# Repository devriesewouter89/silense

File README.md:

View this project on [CADLAB.io](https://cadlab.io/project/2243). 

# silense

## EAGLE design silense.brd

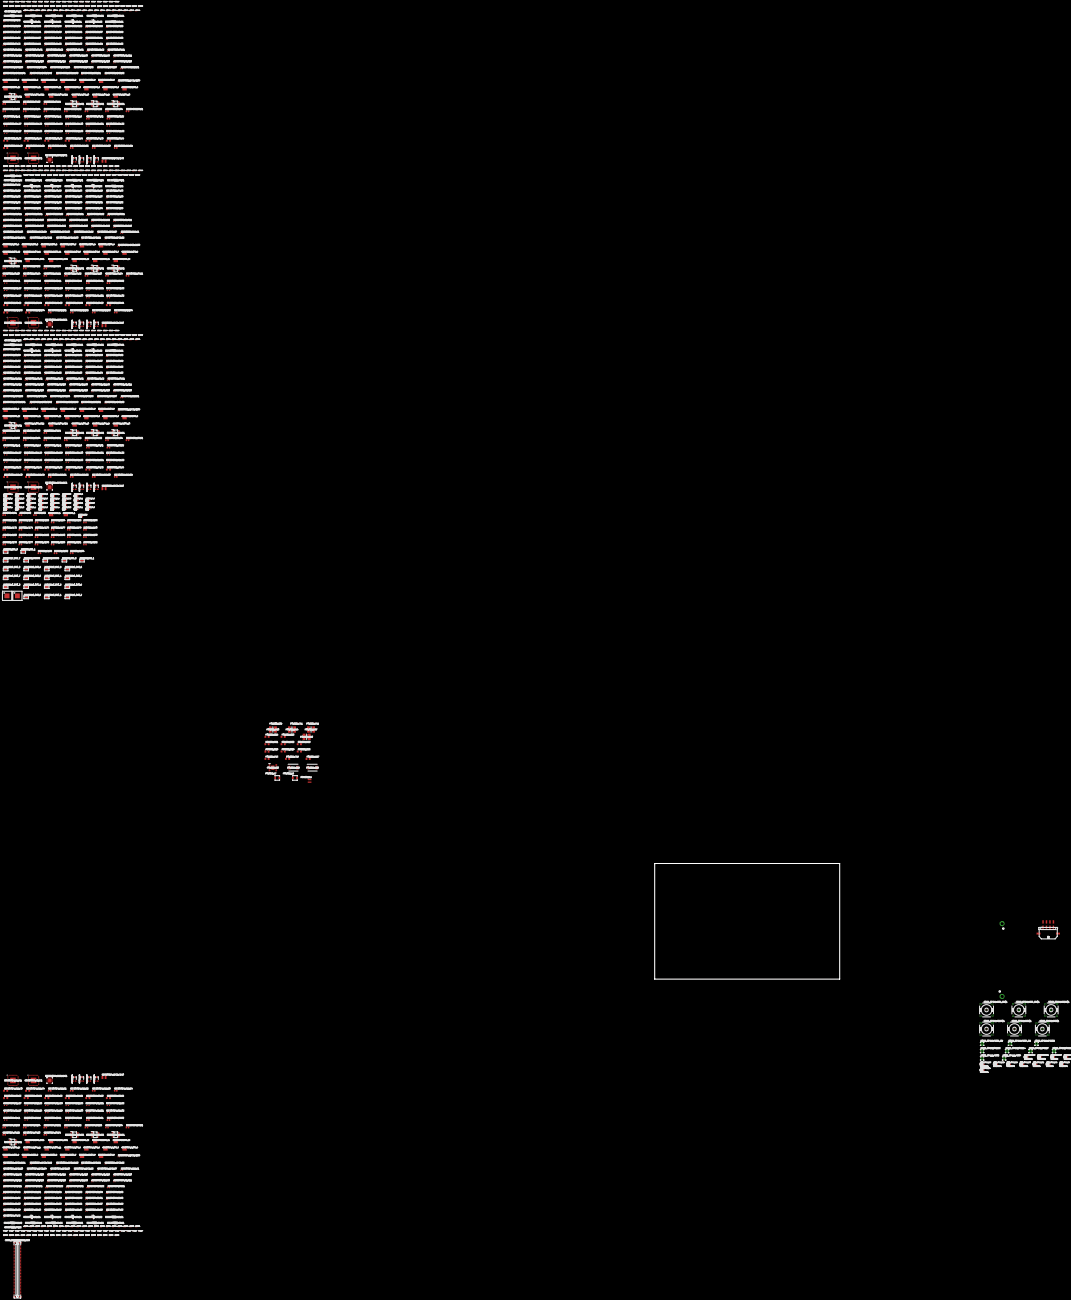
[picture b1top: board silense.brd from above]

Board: 2 copper layers, 946 parts (0 on the bottom side), 798 nets, no tracks yet.

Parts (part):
CONN_FPGA1:D3, CONN_FPGA1:D4, CONN_FPGA1:D13, CONN_FPGA1:D14, CONN_FPGA1:D17, CONN_FPGA1:D18, CONN_FPGA1:D19, CONN_FPGA1:D20: SBR1U200P1; POWERDI-123
CONN_FPGA1:D15, CONN_FPGA1:D16, CONN_FPGA1:D21, CONN_FPGA1:D22: SBR3U20SA; POWERDI-123
CONN_FPGA1:HVM$1, CONN_FPGA1:HVM_CW$1, CONN_FPGA1:HVP$1, CONN_FPGA1:HVP_CW$1, CONN_FPGA1:VDDM$1, CONN_FPGA1:VDDP$1: R141426
CONN_FPGA1:J1: FMC-LPC; FMC-LPC-MALE
CONN_FPGA1:PGND+: GND; 3,17/1,3
CONN_FPGA1:PGND-, CONN_FPGA1:PGNDD, CONN_FPGA1:PHVM, CONN_FPGA1:PHVM_CW, CONN_FPGA1:PHVP, CONN_FPGA1:PHVP_CW, CONN_FPGA1:PVDDM, CONN_FPGA1:PVDDP: 3,17/1,3
CONN_FPGA1:POWER_BOARD_CONN: 43045-0809
CONN_RESONATORS1:C30: CBEC219-3479B001C1AF; BTB_CONN_68_F
DRIVER1:C170, DRIVER1:C172, DRIVER1:C174, DRIVER1:C175, DRIVER1:C177, DRIVER1:C178, DRIVER1:C180, DRIVER1:C181, DRIVER1:C182, DRIVER1:C183, DRIVER1:C184, DRIVER1:C185, DRIVER1:C190, DRIVER1:C191, DRIVER2:C170, DRIVER2:C172, DRIVER2:C174, DRIVER2:C175, DRIVER2:C177, DRIVER2:C178, DRIVER2:C180, DRIVER2:C181, DRIVER2:C182, DRIVER2:C183, DRIVER2:C184, DRIVER2:C185, DRIVER2:C190, DRIVER2:C191: 220n 100V; C0805
DRIVER1:D0_0, DRIVER1:D0_1, DRIVER1:D1_0, DRIVER1:D1_1, DRIVER1:D2_0, DRIVER1:D2_1, DRIVER1:D3_0, DRIVER1:D3_1, DRIVER1:D4_0, DRIVER1:D4_1, DRIVER1:D5_0, DRIVER1:D5_1, DRIVER1:D6_0, DRIVER1:D6_1, DRIVER1:D7_0, DRIVER1:D7_1, DRIVER2:D0_0, DRIVER2:D0_1, DRIVER2:D1_0, DRIVER2:D1_1, DRIVER2:D2_0, DRIVER2:D2_1, DRIVER2:D3_0, DRIVER2:D3_1, DRIVER2:D4_0, DRIVER2:D4_1, DRIVER2:D5_0, DRIVER2:D5_1, DRIVER2:D6_0, DRIVER2:D6_1, DRIVER2:D7_0, DRIVER2:D7_1: POWERDI-123
DRIVER1:GND_1, DRIVER2:GND_1: 5019; TP380X203
DRIVER1:IN0_0, DRIVER1:IN0_1, DRIVER1:LVOUT0, DRIVER1:T_OUT_0, DRIVER1:T_OUT_1, DRIVER1:T_OUT_2, DRIVER1:T_OUT_3, DRIVER1:T_OUT_4, DRIVER1:T_OUT_5, DRIVER1:T_OUT_6, DRIVER1:T_OUT_7, DRIVER2:IN0_0, DRIVER2:IN0_1, DRIVER2:LVOUT0, DRIVER2:T_OUT_0, DRIVER2:T_OUT_1, DRIVER2:T_OUT_2, DRIVER2:T_OUT_3, DRIVER2:T_OUT_4, DRIVER2:T_OUT_5, DRIVER2:T_OUT_6, DRIVER2:T_OUT_7: 5015; KEYSTONE_5015
DRIVER1:R2, DRIVER2:R2: 10k; R0805
DRIVER1:STHV_0, DRIVER2:STHV_0: STHV800; TFLGA-56LD
POWER1:C39: C3216X7R1H225K160AE; CAPC3216X180N
POWER1:C40, POWER1:C43, POWER1:C44, POWER1:C47: 1206 x7r 47uF 25V; CAPC6050X550N
POWER1:C41, POWER1:C42: 0.1uF x7r 1206; CAPC3416X90N
POWER1:C45, POWER1:C46: 1206 x7r 2.2uF 25V; C1206
POWER1:D25: MBRS360T3G; DIOM7958X256N
POWER1:D26: VS-MBRS340-M3_9AT; DIOM7959X262N
POWER1:IC3: LT8471EFE#PBF; SOP65P640X120-21N
POWER1:L2: 744025150; WE-TPC_282892
POWER1:L7: 74437324068; WE-LHMI_402048
POWER1:L8: 74437324100; WE-LHMI_402048
POWER1:R17: 261k 25V; M1206
POWER1:R18: 82k 25V; M1206
POWER1:R19, POWER1:R21: 316k; R1206
POWER1:R20, POWER1:R22: 59k; R1206
POWER1:R23, POWER1:R24: 100k; R1206
POWER1:R25: 187k; R1206
RECEIVER1:ADC2:ADC1, RECEIVER2:ADC2:ADC1, RECEIVER3:ADC2:ADC1, RECEIVER4:ADC2:ADC1: LTC2344-16; QFN32
RECEIVER1:ADC2:C139, RECEIVER1:ADC2:C142, RECEIVER1:ADC2:C143, RECEIVER2:ADC2:C139, RECEIVER2:ADC2:C142, RECEIVER2:ADC2:C143, RECEIVER3:ADC2:C139, RECEIVER3:ADC2:C142, RECEIVER3:ADC2:C143, RECEIVER4:ADC2:C139, RECEIVER4:ADC2:C142, RECEIVER4:ADC2:C143: 0.1uf; C0402
RECEIVER1:ADC2:C140, RECEIVER2:ADC2:C140, RECEIVER3:ADC2:C140, RECEIVER4:ADC2:C140: 47uf 10V; C1210
RECEIVER1:ADC2:C141, RECEIVER2:ADC2:C141, RECEIVER3:ADC2:C141, RECEIVER4:ADC2:C141: 2.2uf; C0402
RECEIVER1:ADC2:R1, RECEIVER1:ADC2:R2, RECEIVER1:ADC2:R3, RECEIVER1:ADC2:R4, RECEIVER1:ADC2:R5, RECEIVER1:ADC2:R6, RECEIVER1:ADC2:R7, RECEIVER2:ADC2:R1, RECEIVER2:ADC2:R2, RECEIVER2:ADC2:R3, RECEIVER2:ADC2:R4, RECEIVER2:ADC2:R5, RECEIVER2:ADC2:R6, RECEIVER2:ADC2:R7, RECEIVER3:ADC2:R1, RECEIVER3:ADC2:R2, RECEIVER3:ADC2:R3, RECEIVER3:ADC2:R4, RECEIVER3:ADC2:R5, RECEIVER3:ADC2:R6, RECEIVER3:ADC2:R7, RECEIVER4:ADC2:R1, RECEIVER4:ADC2:R2, RECEIVER4:ADC2:R3, RECEIVER4:ADC2:R4, RECEIVER4:ADC2:R5, RECEIVER4:ADC2:R6, RECEIVER4:ADC2:R7: 33R; R0402
RECEIVER1:S1:C1, RECEIVER1:S1:C2, RECEIVER1:S1:C3, RECEIVER1:S1:C4, RECEIVER1:S1:C5, RECEIVER1:S1:C6, RECEIVER1:S1:C7, RECEIVER1:S1:C8, RECEIVER1:S1:C9, RECEIVER1:S1:C10, RECEIVER1:S1:C13, RECEIVER1:S1:C14, RECEIVER1:S1:C15, RECEIVER1:S1:C16, RECEIVER1:S1:C17, RECEIVER1:S1:C18, RECEIVER1:S1:C21, RECEIVER1:S1:C22, RECEIVER1:S1:C23, RECEIVER1:S1:C26, RECEIVER1:S1:C51, RECEIVER1:S1:C52, RECEIVER1:S1:C53, RECEIVER1:S1:C54, RECEIVER1:S1:C55, RECEIVER1:S1:C56, RECEIVER1:S2:C1, RECEIVER1:S2:C2, RECEIVER1:S2:C3, RECEIVER1:S2:C4, RECEIVER1:S2:C5, RECEIVER1:S2:C6, RECEIVER1:S2:C7, RECEIVER1:S2:C8, RECEIVER1:S2:C9, RECEIVER1:S2:C10, RECEIVER1:S2:C13, RECEIVER1:S2:C14, RECEIVER1:S2:C15, RECEIVER1:S2:C16, RECEIVER1:S2:C17, RECEIVER1:S2:C18, RECEIVER1:S2:C21, RECEIVER1:S2:C22, RECEIVER1:S2:C23, RECEIVER1:S2:C26, RECEIVER1:S2:C51, RECEIVER1:S2:C52, RECEIVER1:S2:C53, RECEIVER1:S2:C54, RECEIVER1:S2:C55, RECEIVER1:S2:C56, RECEIVER2:S1:C1, RECEIVER2:S1:C2, RECEIVER2:S1:C3, RECEIVER2:S1:C4, RECEIVER2:S1:C5, RECEIVER2:S1:C6, RECEIVER2:S1:C7, RECEIVER2:S1:C8, RECEIVER2:S1:C9, RECEIVER2:S1:C10, RECEIVER2:S1:C13, RECEIVER2:S1:C14, RECEIVER2:S1:C15, RECEIVER2:S1:C16, RECEIVER2:S1:C17, RECEIVER2:S1:C18, RECEIVER2:S1:C21, RECEIVER2:S1:C22, RECEIVER2:S1:C23, RECEIVER2:S1:C26, RECEIVER2:S1:C51, RECEIVER2:S1:C52, RECEIVER2:S1:C53, RECEIVER2:S1:C54, RECEIVER2:S1:C55, RECEIVER2:S1:C56, RECEIVER2:S2:C1, RECEIVER2:S2:C2, RECEIVER2:S2:C3, RECEIVER2:S2:C4, RECEIVER2:S2:C5, RECEIVER2:S2:C6, RECEIVER2:S2:C7, RECEIVER2:S2:C8, RECEIVER2:S2:C9, RECEIVER2:S2:C10, RECEIVER2:S2:C13, RECEIVER2:S2:C14, RECEIVER2:S2:C15, RECEIVER2:S2:C16, RECEIVER2:S2:C17, RECEIVER2:S2:C18, RECEIVER2:S2:C21, RECEIVER2:S2:C22, RECEIVER2:S2:C23, RECEIVER2:S2:C26, RECEIVER2:S2:C51, RECEIVER2:S2:C52, RECEIVER2:S2:C53, RECEIVER2:S2:C54, RECEIVER2:S2:C55, RECEIVER2:S2:C56, RECEIVER3:S1:C1, RECEIVER3:S1:C2, RECEIVER3:S1:C3, RECEIVER3:S1:C4, RECEIVER3:S1:C5, RECEIVER3:S1:C6, RECEIVER3:S1:C7, RECEIVER3:S1:C8, RECEIVER3:S1:C9, RECEIVER3:S1:C10, RECEIVER3:S1:C13, RECEIVER3:S1:C14, RECEIVER3:S1:C15, RECEIVER3:S1:C16, RECEIVER3:S1:C17, RECEIVER3:S1:C18, RECEIVER3:S1:C21, RECEIVER3:S1:C22, RECEIVER3:S1:C23, RECEIVER3:S1:C26, RECEIVER3:S1:C51, RECEIVER3:S1:C52, RECEIVER3:S1:C53, RECEIVER3:S1:C54, RECEIVER3:S1:C55, RECEIVER3:S1:C56, RECEIVER3:S2:C1, RECEIVER3:S2:C2, RECEIVER3:S2:C3, RECEIVER3:S2:C4, RECEIVER3:S2:C5, RECEIVER3:S2:C6, RECEIVER3:S2:C7, RECEIVER3:S2:C8, RECEIVER3:S2:C9, RECEIVER3:S2:C10, RECEIVER3:S2:C13, RECEIVER3:S2:C14, RECEIVER3:S2:C15, RECEIVER3:S2:C16, RECEIVER3:S2:C17, RECEIVER3:S2:C18, RECEIVER3:S2:C21, RECEIVER3:S2:C22, RECEIVER3:S2:C23, RECEIVER3:S2:C26, RECEIVER3:S2:C51, RECEIVER3:S2:C52, RECEIVER3:S2:C53, RECEIVER3:S2:C54, RECEIVER3:S2:C55, RECEIVER3:S2:C56, RECEIVER4:S1:C1, RECEIVER4:S1:C2, RECEIVER4:S1:C3, RECEIVER4:S1:C4, RECEIVER4:S1:C5, RECEIVER4:S1:C6, RECEIVER4:S1:C7, RECEIVER4:S1:C8, RECEIVER4:S1:C9, RECEIVER4:S1:C10, RECEIVER4:S1:C13, RECEIVER4:S1:C14, RECEIVER4:S1:C15, RECEIVER4:S1:C16, RECEIVER4:S1:C17, RECEIVER4:S1:C18, RECEIVER4:S1:C21, RECEIVER4:S1:C22, RECEIVER4:S1:C23, RECEIVER4:S1:C26, RECEIVER4:S1:C51, RECEIVER4:S1:C52, RECEIVER4:S1:C53, RECEIVER4:S1:C54, RECEIVER4:S1:C55, RECEIVER4:S1:C56, RECEIVER4:S2:C1, RECEIVER4:S2:C2, RECEIVER4:S2:C3, RECEIVER4:S2:C4, RECEIVER4:S2:C5, RECEIVER4:S2:C6, RECEIVER4:S2:C7, RECEIVER4:S2:C8, RECEIVER4:S2:C9, RECEIVER4:S2:C10, RECEIVER4:S2:C13, RECEIVER4:S2:C14, RECEIVER4:S2:C15, RECEIVER4:S2:C16, RECEIVER4:S2:C17, RECEIVER4:S2:C18, RECEIVER4:S2:C21, RECEIVER4:S2:C22, RECEIVER4:S2:C23, RECEIVER4:S2:C26, RECEIVER4:S2:C51, RECEIVER4:S2:C52, RECEIVER4:S2:C53, RECEIVER4:S2:C54, RECEIVER4:S2:C55, RECEIVER4:S2:C56: 0.1uF; WCAP-CSGP_0402
RECEIVER1:S1:C11, RECEIVER1:S1:C12, RECEIVER1:S2:C11, RECEIVER1:S2:C12, RECEIVER2:S1:C11, RECEIVER2:S1:C12, RECEIVER2:S2:C11, RECEIVER2:S2:C12, RECEIVER3:S1:C11, RECEIVER3:S1:C12, RECEIVER3:S2:C11, RECEIVER3:S2:C12, RECEIVER4:S1:C11, RECEIVER4:S1:C12, RECEIVER4:S2:C11, RECEIVER4:S2:C12: 18nF; WCAP-CSGP_0402
RECEIVER1:S1:C19, RECEIVER1:S1:C20, RECEIVER1:S2:C19, RECEIVER1:S2:C20, RECEIVER2:S1:C19, RECEIVER2:S1:C20, RECEIVER2:S2:C19, RECEIVER2:S2:C20, RECEIVER3:S1:C19, RECEIVER3:S1:C20, RECEIVER3:S2:C19, RECEIVER3:S2:C20, RECEIVER4:S1:C19, RECEIVER4:S1:C20, RECEIVER4:S2:C19, RECEIVER4:S2:C20: 10nF; WCAP-CSGP_0402
RECEIVER1:S1:C24, RECEIVER1:S1:C27, RECEIVER1:S2:C24, RECEIVER1:S2:C27, RECEIVER2:S1:C24, RECEIVER2:S1:C27, RECEIVER2:S2:C24, RECEIVER2:S2:C27, RECEIVER3:S1:C24, RECEIVER3:S1:C27, RECEIVER3:S2:C24, RECEIVER3:S2:C27, RECEIVER4:S1:C24, RECEIVER4:S1:C27, RECEIVER4:S2:C24, RECEIVER4:S2:C27: 22pF; WCAP-CSGP_0402
RECEIVER1:S1:D1, RECEIVER1:S1:D2, RECEIVER1:S2:D1, RECEIVER1:S2:D2, RECEIVER2:S1:D1, RECEIVER2:S1:D2, RECEIVER2:S2:D1, RECEIVER2:S2:D2, RECEIVER3:S1:D1, RECEIVER3:S1:D2, RECEIVER3:S2:D1, RECEIVER3:S2:D2, RECEIVER4:S1:D1, RECEIVER4:S1:D2, RECEIVER4:S2:D1, RECEIVER4:S2:D2: BAT64-04E6433; SOT95P260X110-3N
RECEIVER1:S1:IC1, RECEIVER1:S2:IC1, RECEIVER2:S1:IC1, RECEIVER2:S2:IC1, RECEIVER3:S1:IC1, RECEIVER3:S2:IC1, RECEIVER4:S1:IC1, RECEIVER4:S2:IC1: AD8334ACPZ; QFN50P900X900X100-65N
RECEIVER1:S1:L1, RECEIVER1:S1:L6, RECEIVER1:S1:L27, RECEIVER1:S1:L28, RECEIVER1:S1:L29, RECEIVER1:S1:L30, RECEIVER1:S1:L31, RECEIVER1:S1:L32, RECEIVER1:S2:L1, RECEIVER1:S2:L6, RECEIVER1:S2:L27, RECEIVER1:S2:L28, RECEIVER1:S2:L29, RECEIVER1:S2:L30, RECEIVER1:S2:L31, RECEIVER1:S2:L32, RECEIVER2:S1:L1, RECEIVER2:S1:L6, RECEIVER2:S1:L27, RECEIVER2:S1:L28, RECEIVER2:S1:L29, RECEIVER2:S1:L30, RECEIVER2:S1:L31, RECEIVER2:S1:L32, RECEIVER2:S2:L1, RECEIVER2:S2:L6, RECEIVER2:S2:L27, RECEIVER2:S2:L28, RECEIVER2:S2:L29, RECEIVER2:S2:L30, RECEIVER2:S2:L31, RECEIVER2:S2:L32, RECEIVER3:S1:L1, RECEIVER3:S1:L6, RECEIVER3:S1:L27, RECEIVER3:S1:L28, RECEIVER3:S1:L29, RECEIVER3:S1:L30, RECEIVER3:S1:L31, RECEIVER3:S1:L32, RECEIVER3:S2:L1, RECEIVER3:S2:L6, RECEIVER3:S2:L27, RECEIVER3:S2:L28, RECEIVER3:S2:L29, RECEIVER3:S2:L30, RECEIVER3:S2:L31, RECEIVER3:S2:L32, RECEIVER4:S1:L1, RECEIVER4:S1:L6, RECEIVER4:S1:L27, RECEIVER4:S1:L28, RECEIVER4:S1:L29, RECEIVER4:S1:L30, RECEIVER4:S1:L31, RECEIVER4:S1:L32, RECEIVER4:S2:L1, RECEIVER4:S2:L6, RECEIVER4:S2:L27, RECEIVER4:S2:L28, RECEIVER4:S2:L29, RECEIVER4:S2:L30, RECEIVER4:S2:L31, RECEIVER4:S2:L32: BLM21AG121SN1D; L2012C
RECEIVER1:S1:R1, RECEIVER1:S1:R3, RECEIVER1:S2:R1, RECEIVER1:S2:R3, RECEIVER2:S1:R1, RECEIVER2:S1:R3, RECEIVER2:S2:R1, RECEIVER2:S2:R3, RECEIVER3:S1:R1, RECEIVER3:S1:R3, RECEIVER3:S2:R1, RECEIVER3:S2:R3, RECEIVER4:S1:R1, RECEIVER4:S1:R3, RECEIVER4:S2:R1, RECEIVER4:S2:R3: 39K; R0402
RECEIVER1:S1:R2, RECEIVER1:S1:R7, RECEIVER1:S1:R8, RECEIVER1:S1:R11, RECEIVER1:S2:R2, RECEIVER1:S2:R7, RECEIVER1:S2:R8, RECEIVER1:S2:R11, RECEIVER2:S1:R2, RECEIVER2:S1:R7, RECEIVER2:S1:R8, RECEIVER2:S1:R11, RECEIVER2:S2:R2, RECEIVER2:S2:R7, RECEIVER2:S2:R8, RECEIVER2:S2:R11, RECEIVER3:S1:R2, RECEIVER3:S1:R7, RECEIVER3:S1:R8, RECEIVER3:S1:R11, RECEIVER3:S2:R2, RECEIVER3:S2:R7, RECEIVER3:S2:R8, RECEIVER3:S2:R11, RECEIVER4:S1:R2, RECEIVER4:S1:R7, RECEIVER4:S1:R8, RECEIVER4:S1:R11, RECEIVER4:S2:R2, RECEIVER4:S2:R7, RECEIVER4:S2:R8, RECEIVER4:S2:R11: 0R; R0402
RECEIVER1:S1:R4, RECEIVER1:S1:R5, RECEIVER1:S2:R4, RECEIVER1:S2:R5, RECEIVER2:S1:R4, RECEIVER2:S1:R5, RECEIVER2:S2:R4, RECEIVER2:S2:R5, RECEIVER3:S1:R4, RECEIVER3:S1:R5, RECEIVER3:S2:R4, RECEIVER3:S2:R5, RECEIVER4:S1:R4, RECEIVER4:S1:R5, RECEIVER4:S2:R4, RECEIVER4:S2:R5: 4K02; R0402
RECEIVER1:S1:R6, RECEIVER1:S1:R10, RECEIVER1:S2:R6, RECEIVER1:S2:R10, RECEIVER2:S1:R6, RECEIVER2:S1:R10, RECEIVER2:S2:R6, RECEIVER2:S2:R10, RECEIVER3:S1:R6, RECEIVER3:S1:R10, RECEIVER3:S2:R6, RECEIVER3:S2:R10, RECEIVER4:S1:R6, RECEIVER4:S1:R10, RECEIVER4:S2:R6, RECEIVER4:S2:R10: DNP; R0402
RECEIVER1:S1:R9, RECEIVER1:S1:R13, RECEIVER1:S2:R9, RECEIVER1:S2:R13, RECEIVER2:S1:R9, RECEIVER2:S1:R13, RECEIVER2:S2:R9, RECEIVER2:S2:R13, RECEIVER3:S1:R9, RECEIVER3:S1:R13, RECEIVER3:S2:R9, RECEIVER3:S2:R13, RECEIVER4:S1:R9, RECEIVER4:S1:R13, RECEIVER4:S2:R9, RECEIVER4:S2:R13: 1K; R0402
RECEIVER1:S1:R12, RECEIVER1:S1:R15, RECEIVER1:S2:R12, RECEIVER1:S2:R15, RECEIVER2:S1:R12, RECEIVER2:S1:R15, RECEIVER2:S2:R12, RECEIVER2:S2:R15, RECEIVER3:S1:R12, RECEIVER3:S1:R15, RECEIVER3:S2:R12, RECEIVER3:S2:R15, RECEIVER4:S1:R12, RECEIVER4:S1:R15, RECEIVER4:S2:R12, RECEIVER4:S2:R15: 274R; R0402
RECEIVER1:S1:TP2_5, RECEIVER1:S1:TP2_6, RECEIVER1:S1:TP2_7, RECEIVER1:S1:TP2_8, RECEIVER1:S1:TP2_9, RECEIVER1:S1:TP2_10, RECEIVER1:S1:TP2_11, RECEIVER1:S1:TP2_12, RECEIVER1:S1:TP2_GND1, RECEIVER1:S2:TP2_5, RECEIVER1:S2:TP2_6, RECEIVER1:S2:TP2_7, RECEIVER1:S2:TP2_8, RECEIVER1:S2:TP2_9, RECEIVER1:S2:TP2_10, RECEIVER1:S2:TP2_11, RECEIVER1:S2:TP2_12, RECEIVER1:S2:TP2_GND1, RECEIVER2:S1:TP2_5, RECEIVER2:S1:TP2_6, RECEIVER2:S1:TP2_7, RECEIVER2:S1:TP2_8, RECEIVER2:S1:TP2_9, RECEIVER2:S1:TP2_10, RECEIVER2:S1:TP2_11, RECEIVER2:S1:TP2_12, RECEIVER2:S1:TP2_GND1, RECEIVER2:S2:TP2_5, RECEIVER2:S2:TP2_6, RECEIVER2:S2:TP2_7, RECEIVER2:S2:TP2_8, RECEIVER2:S2:TP2_9, RECEIVER2:S2:TP2_10, RECEIVER2:S2:TP2_11, RECEIVER2:S2:TP2_12, RECEIVER2:S2:TP2_GND1, RECEIVER3:S1:TP2_5, RECEIVER3:S1:TP2_6, RECEIVER3:S1:TP2_7, RECEIVER3:S1:TP2_8, RECEIVER3:S1:TP2_9, RECEIVER3:S1:TP2_10, RECEIVER3:S1:TP2_11, RECEIVER3:S1:TP2_12, RECEIVER3:S1:TP2_GND1, RECEIVER3:S2:TP2_5, RECEIVER3:S2:TP2_6, RECEIVER3:S2:TP2_7, RECEIVER3:S2:TP2_8, RECEIVER3:S2:TP2_9, RECEIVER3:S2:TP2_10, RECEIVER3:S2:TP2_11, RECEIVER3:S2:TP2_12, RECEIVER3:S2:TP2_GND1, RECEIVER4:S1:TP2_5, RECEIVER4:S1:TP2_6, RECEIVER4:S1:TP2_7, RECEIVER4:S1:TP2_8, RECEIVER4:S1:TP2_9, RECEIVER4:S1:TP2_10, RECEIVER4:S1:TP2_11, RECEIVER4:S1:TP2_12, RECEIVER4:S1:TP2_GND1, RECEIVER4:S2:TP2_5, RECEIVER4:S2:TP2_6, RECEIVER4:S2:TP2_7, RECEIVER4:S2:TP2_8, RECEIVER4:S2:TP2_9, RECEIVER4:S2:TP2_10, RECEIVER4:S2:TP2_11, RECEIVER4:S2:TP2_12, RECEIVER4:S2:TP2_GND1: 5019; TP380X203
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
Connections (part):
BUSY: CONN_FPGA1:J1.C26, CONN_FPGA1:J1.C27, CONN_FPGA1:J1.D26, CONN_FPGA1:J1.D27, RECEIVER1:ADC2:R2.2, RECEIVER2:ADC2:R2.2, RECEIVER3:ADC2:R2.2, RECEIVER4:ADC2:R2.2
CNV: CONN_FPGA1:J1.G36, CONN_FPGA1:J1.G37, CONN_FPGA1:J1.H37, CONN_FPGA1:J1.H38, RECEIVER1:ADC2:ADC1.15, RECEIVER2:ADC2:ADC1.15, RECEIVER3:ADC2:ADC1.15, RECEIVER4:ADC2:ADC1.15
CONN_FPGA1:3P3V: CONN_FPGA1:J1.C39, CONN_FPGA1:J1.D40
CONN_FPGA1:GND: CONN_FPGA1:HVM$1.2, CONN_FPGA1:HVM$1.3, CONN_FPGA1:HVM$1.4, CONN_FPGA1:HVM$1.5, CONN_FPGA1:HVM_CW$1.2, CONN_FPGA1:HVM_CW$1.3, CONN_FPGA1:HVM_CW$1.4, CONN_FPGA1:HVM_CW$1.5, CONN_FPGA1:HVP$1.2, CONN_FPGA1:HVP$1.3, CONN_FPGA1:HVP$1.4, CONN_FPGA1:HVP$1.5, CONN_FPGA1:HVP_CW$1.2, CONN_FPGA1:HVP_CW$1.3, CONN_FPGA1:HVP_CW$1.4, CONN_FPGA1:HVP_CW$1.5, CONN_FPGA1:J1.C1, CONN_FPGA1:J1.C4, CONN_FPGA1:J1.C5, CONN_FPGA1:J1.C8, CONN_FPGA1:J1.C9, CONN_FPGA1:J1.C12, CONN_FPGA1:J1.C13, CONN_FPGA1:J1.C16, CONN_FPGA1:J1.C17, CONN_FPGA1:J1.C20, CONN_FPGA1:J1.C21, CONN_FPGA1:J1.C24, CONN_FPGA1:J1.C25, CONN_FPGA1:J1.C28, CONN_FPGA1:J1.C29, CONN_FPGA1:J1.C32, CONN_FPGA1:J1.C33, CONN_FPGA1:J1.C36, CONN_FPGA1:J1.C38, CONN_FPGA1:J1.C40, CONN_FPGA1:J1.D2, CONN_FPGA1:J1.D3, CONN_FPGA1:J1.D6, CONN_FPGA1:J1.D7, CONN_FPGA1:J1.D10, CONN_FPGA1:J1.D13, CONN_FPGA1:J1.D16, CONN_FPGA1:J1.D19, CONN_FPGA1:J1.D22, CONN_FPGA1:J1.D25, CONN_FPGA1:J1.D28, CONN_FPGA1:J1.D37, CONN_FPGA1:J1.D39, CONN_FPGA1:J1.G1, CONN_FPGA1:J1.H3, CONN_FPGA1:J1.H6, CONN_FPGA1:J1.H9, CONN_FPGA1:J1.H12, CONN_FPGA1:J1.H15, CONN_FPGA1:J1.H18, CONN_FPGA1:J1.H21, CONN_FPGA1:J1.H24, CONN_FPGA1:J1.H27, CONN_FPGA1:J1.H30, CONN_FPGA1:J1.H33, CONN_FPGA1:J1.H36, CONN_FPGA1:J1.H39, CONN_FPGA1:PGND+.1, CONN_FPGA1:PGND-.1, CONN_FPGA1:PGNDD.1, CONN_FPGA1:POWER_BOARD_CONN.P$4, CONN_FPGA1:POWER_BOARD_CONN.P$8, CONN_FPGA1:VDDM$1.2, CONN_FPGA1:VDDM$1.3, CONN_FPGA1:VDDM$1.4, CONN_FPGA1:VDDM$1.5, CONN_FPGA1:VDDP$1.2, CONN_FPGA1:VDDP$1.3, CONN_FPGA1:VDDP$1.4, CONN_FPGA1:VDDP$1.5
CONN_FPGA1:HVM: CONN_FPGA1:D4.A, CONN_FPGA1:D18.A, CONN_FPGA1:POWER_BOARD_CONN.P$5
CONN_FPGA1:HVM_CW: CONN_FPGA1:D3.A, CONN_FPGA1:D17.A, CONN_FPGA1:POWER_BOARD_CONN.P$6
CONN_FPGA1:HVP: CONN_FPGA1:D13.C, CONN_FPGA1:D19.C, CONN_FPGA1:POWER_BOARD_CONN.P$1
CONN_FPGA1:HVP_CW: CONN_FPGA1:D14.C, CONN_FPGA1:D20.C, CONN_FPGA1:POWER_BOARD_CONN.P$2
CONN_FPGA1:N$1: CONN_FPGA1:J1.G4, CONN_FPGA1:J1.G5, CONN_FPGA1:J1.G8, CONN_FPGA1:J1.G11, CONN_FPGA1:J1.G14, CONN_FPGA1:J1.G17, CONN_FPGA1:J1.G20, CONN_FPGA1:J1.G23, CONN_FPGA1:J1.G26, CONN_FPGA1:J1.G29, CONN_FPGA1:J1.G32, CONN_FPGA1:J1.G35, CONN_FPGA1:J1.G38, CONN_FPGA1:J1.G40
CONN_FPGA1:N$3: CONN_FPGA1:D17.C, CONN_FPGA1:PHVM_CW.1
CONN_FPGA1:N$4: CONN_FPGA1:D18.C, CONN_FPGA1:PHVM.1
CONN_FPGA1:N$17: CONN_FPGA1:D3.C, CONN_FPGA1:HVM_CW$1.1
CONN_FPGA1:N$18: CONN_FPGA1:D4.C, CONN_FPGA1:HVM$1.1
CONN_FPGA1:N$19: CONN_FPGA1:D13.A, CONN_FPGA1:HVP$1.1
CONN_FPGA1:N$20: CONN_FPGA1:D14.A, CONN_FPGA1:HVP_CW$1.1
CONN_FPGA1:N$21: CONN_FPGA1:D15.A, CONN_FPGA1:VDDP$1.1
CONN_FPGA1:N$22: CONN_FPGA1:D16.C, CONN_FPGA1:VDDM$1.1
CONN_FPGA1:N$25: CONN_FPGA1:D19.A, CONN_FPGA1:PHVP.1
CONN_FPGA1:N$26: CONN_FPGA1:D20.A, CONN_FPGA1:PHVP_CW.1
CONN_FPGA1:N$27: CONN_FPGA1:D21.A, CONN_FPGA1:PVDDP.1
CONN_FPGA1:N$28: CONN_FPGA1:D22.C, CONN_FPGA1:PVDDM.1
CONN_FPGA1:VDDM: CONN_FPGA1:D16.A, CONN_FPGA1:D22.A, CONN_FPGA1:POWER_BOARD_CONN.P$7
CONN_FPGA1:VDDP: CONN_FPGA1:D15.C, CONN_FPGA1:D21.C, CONN_FPGA1:POWER_BOARD_CONN.P$3
CONN_RESONATORS1:GND: CONN_RESONATORS1:C30.1, CONN_RESONATORS1:C30.34, CONN_RESONATORS1:C30.35, CONN_RESONATORS1:C30.68
CW: CONN_FPGA1:J1.H31, DRIVER1:STHV_0.CW, DRIVER2:STHV_0.CW
DRIVER1:GND: DRIVER1:C170.2, DRIVER1:C172.1, DRIVER1:C174.1, DRIVER1:C175.1, DRIVER1:C177.1, DRIVER1:C178.1, DRIVER1:C180.2, DRIVER1:C181.2, DRIVER1:C182.2, DRIVER1:C183.2, DRIVER1:C184.2, DRIVER1:C185.2, DRIVER1:C190.1, DRIVER1:C191.1, DRIVER1:GND_1.1, DRIVER1:STHV_0.AGND, DRIVER1:STHV_0.DGND, DRIVER1:STHV_0.GND_PWR@1, DRIVER1:STHV_0.GND_PWR@2, DRIVER1:STHV_0.GND_PWR@3, DRIVER1:STHV_0.GND_PWR@4
DRIVER1:HVM: DRIVER1:C183.1, DRIVER1:C184.1, DRIVER1:C185.1, DRIVER1:D0_1.A, DRIVER1:D1_1.A, DRIVER1:D2_1.A, DRIVER1:D3_1.A, DRIVER1:D4_1.A, DRIVER1:D5_1.A, DRIVER1:D6_1.A, DRIVER1:D7_1.A, DRIVER1:STHV_0.HVM@1, DRIVER1:STHV_0.HVM@2, DRIVER1:STHV_0.HVM@3, DRIVER1:STHV_0.HVM@4, DRIVER1:STHV_0.HVM@5
DRIVER1:HVM_CW: DRIVER1:C190.2, DRIVER1:C191.2, DRIVER1:STHV_0.HVM_CW
DRIVER1:HVP: DRIVER1:C172.2, DRIVER1:C174.2, DRIVER1:C175.2, DRIVER1:D0_0.C, DRIVER1:D1_0.C, DRIVER1:D2_0.C, DRIVER1:D3_0.C, DRIVER1:D4_0.C, DRIVER1:D5_0.C, DRIVER1:D6_0.C, DRIVER1:D7_0.C, DRIVER1:STHV_0.HVP@1, DRIVER1:STHV_0.HVP@2, DRIVER1:STHV_0.HVP@3, DRIVER1:STHV_0.HVP@4, DRIVER1:STHV_0.HVP@5
DRIVER1:HVP_CW: DRIVER1:C177.2, DRIVER1:C178.2, DRIVER1:STHV_0.HVP_CW
DRIVER1:N$23: DRIVER1:R2.1, DRIVER1:STHV_0.THSD
DRIVER1:N$24: DRIVER1:C170.1, DRIVER1:STHV_0.SUB
DRIVER1:VDDM: DRIVER1:C181.1, DRIVER1:STHV_0.VDDM
DRIVER1:VDDP: DRIVER1:C180.1, DRIVER1:C182.1, DRIVER1:R2.2, DRIVER1:STHV_0.DVDD, DRIVER1:STHV_0.VDDP
DRIVER2:GND: DRIVER2:C170.2, DRIVER2:C172.1, DRIVER2:C174.1, DRIVER2:C175.1, DRIVER2:C177.1, DRIVER2:C178.1, DRIVER2:C180.2, DRIVER2:C181.2, DRIVER2:C182.2, DRIVER2:C183.2, DRIVER2:C184.2, DRIVER2:C185.2, DRIVER2:C190.1, DRIVER2:C191.1, DRIVER2:GND_1.1, DRIVER2:STHV_0.AGND, DRIVER2:STHV_0.DGND, DRIVER2:STHV_0.GND_PWR@1, DRIVER2:STHV_0.GND_PWR@2, DRIVER2:STHV_0.GND_PWR@3, DRIVER2:STHV_0.GND_PWR@4
DRIVER2:HVM: DRIVER2:C183.1, DRIVER2:C184.1, DRIVER2:C185.1, DRIVER2:D0_1.A, DRIVER2:D1_1.A, DRIVER2:D2_1.A, DRIVER2:D3_1.A, DRIVER2:D4_1.A, DRIVER2:D5_1.A, DRIVER2:D6_1.A, DRIVER2:D7_1.A, DRIVER2:STHV_0.HVM@1, DRIVER2:STHV_0.HVM@2, DRIVER2:STHV_0.HVM@3, DRIVER2:STHV_0.HVM@4, DRIVER2:STHV_0.HVM@5
DRIVER2:HVM_CW: DRIVER2:C190.2, DRIVER2:C191.2, DRIVER2:STHV_0.HVM_CW
DRIVER2:HVP: DRIVER2:C172.2, DRIVER2:C174.2, DRIVER2:C175.2, DRIVER2:D0_0.C, DRIVER2:D1_0.C, DRIVER2:D2_0.C, DRIVER2:D3_0.C, DRIVER2:D4_0.C, DRIVER2:D5_0.C, DRIVER2:D6_0.C, DRIVER2:D7_0.C, DRIVER2:STHV_0.HVP@1, DRIVER2:STHV_0.HVP@2, DRIVER2:STHV_0.HVP@3, DRIVER2:STHV_0.HVP@4, DRIVER2:STHV_0.HVP@5
DRIVER2:HVP_CW: DRIVER2:C177.2, DRIVER2:C178.2, DRIVER2:STHV_0.HVP_CW
DRIVER2:N$23: DRIVER2:R2.1, DRIVER2:STHV_0.THSD
DRIVER2:N$24: DRIVER2:C170.1, DRIVER2:STHV_0.SUB
DRIVER2:VDDM: DRIVER2:C181.1, DRIVER2:STHV_0.VDDM
DRIVER2:VDDP: DRIVER2:C180.1, DRIVER2:C182.1, DRIVER2:R2.2, DRIVER2:STHV_0.DVDD, DRIVER2:STHV_0.VDDP
unnamed: DRIVER2:STHV_0.LVOUT_4, RECEIVER3:S2:D2.3, RECEIVER3:S2:L6.1
unnamed: DRIVER2:STHV_0.LVOUT_3, RECEIVER3:S2:D1.3, RECEIVER3:S2:L1.1
unnamed: DRIVER2:STHV_0.LVOUT_2, RECEIVER3:S1:D2.3, RECEIVER3:S1:L6.1
unnamed: DRIVER2:LVOUT0.1, DRIVER2:STHV_0.LVOUT_1, RECEIVER3:S1:D1.3, RECEIVER3:S1:L1.1
unnamed: DRIVER2:STHV_0.LVOUT_5, RECEIVER4:S1:D1.3, RECEIVER4:S1:L1.1
unnamed: DRIVER2:STHV_0.LVOUT_6, RECEIVER4:S1:D2.3, RECEIVER4:S1:L6.1
unnamed: DRIVER2:STHV_0.LVOUT_7, RECEIVER4:S2:D1.3, RECEIVER4:S2:L1.1
unnamed: DRIVER2:STHV_0.LVOUT_8, RECEIVER4:S2:D2.3, RECEIVER4:S2:L6.1
unnamed: DRIVER1:LVOUT0.1, DRIVER1:STHV_0.LVOUT_1, RECEIVER1:S1:D1.3, RECEIVER1:S1:L1.1
unnamed: DRIVER1:STHV_0.LVOUT_2, RECEIVER1:S1:D2.3, RECEIVER1:S1:L6.1
unnamed: DRIVER1:STHV_0.LVOUT_3, RECEIVER1:S2:D1.3, RECEIVER1:S2:L1.1
unnamed: DRIVER1:STHV_0.LVOUT_4, RECEIVER1:S2:D2.3, RECEIVER1:S2:L6.1
unnamed: DRIVER1:STHV_0.LVOUT_5, RECEIVER2:S1:D1.3, RECEIVER2:S1:L1.1
unnamed: DRIVER1:STHV_0.LVOUT_6, RECEIVER2:S1:D2.3, RECEIVER2:S1:L6.1
unnamed: DRIVER1:STHV_0.LVOUT_7, RECEIVER2:S2:D1.3, RECEIVER2:S2:L1.1
unnamed: DRIVER1:STHV_0.LVOUT_8, RECEIVER2:S2:D2.3, RECEIVER2:S2:L6.1
unnamed: CONN_FPGA1:J1.G31, DRIVER2:STHV_0.IN8_1
unnamed: CONN_FPGA1:J1.G30, DRIVER2:STHV_0.IN8_0
unnamed: CONN_FPGA1:J1.H29, DRIVER2:STHV_0.IN7_1
unnamed: CONN_FPGA1:J1.H28, DRIVER2:STHV_0.IN7_0
unnamed: CONN_FPGA1:J1.G28, DRIVER2:STHV_0.IN6_1
unnamed: CONN_FPGA1:J1.G27, DRIVER2:STHV_0.IN6_0
unnamed: CONN_FPGA1:J1.H26, DRIVER2:STHV_0.IN5_1
unnamed: CONN_FPGA1:J1.H25, DRIVER2:STHV_0.IN5_0
unnamed: CONN_FPGA1:J1.G25, DRIVER2:STHV_0.IN4_1
unnamed: CONN_FPGA1:J1.G24, DRIVER2:STHV_0.IN4_0
unnamed: CONN_FPGA1:J1.H23, DRIVER2:STHV_0.IN3_1
unnamed: CONN_FPGA1:J1.H22, DRIVER2:STHV_0.IN3_0
unnamed: CONN_FPGA1:J1.G22, DRIVER2:STHV_0.IN2_1
unnamed: CONN_FPGA1:J1.G21, DRIVER2:STHV_0.IN2_0
unnamed: CONN_FPGA1:J1.H20, DRIVER2:IN0_1.1, DRIVER2:STHV_0.IN1_1
unnamed: CONN_FPGA1:J1.H19, DRIVER2:IN0_0.1, DRIVER2:STHV_0.IN1_0
unnamed: CONN_FPGA1:J1.G19, DRIVER1:STHV_0.IN8_1
unnamed: CONN_FPGA1:J1.G18, DRIVER1:STHV_0.IN8_0
unnamed: CONN_FPGA1:J1.H17, DRIVER1:STHV_0.IN7_1
unnamed: CONN_FPGA1:J1.H16, DRIVER1:STHV_0.IN7_0
unnamed: CONN_FPGA1:J1.G16, DRIVER1:STHV_0.IN6_1
unnamed: CONN_FPGA1:J1.G15, DRIVER1:STHV_0.IN6_0
unnamed: CONN_FPGA1:J1.H14, DRIVER1:STHV_0.IN5_1
unnamed: CONN_FPGA1:J1.H13, DRIVER1:STHV_0.IN5_0
unnamed: CONN_FPGA1:J1.G13, DRIVER1:STHV_0.IN4_1
unnamed: CONN_FPGA1:J1.G12, DRIVER1:STHV_0.IN4_0
unnamed: CONN_FPGA1:J1.H11, DRIVER1:STHV_0.IN3_1
unnamed: CONN_FPGA1:J1.H10, DRIVER1:STHV_0.IN3_0
unnamed: CONN_FPGA1:J1.G10, DRIVER1:STHV_0.IN2_1
unnamed: CONN_FPGA1:J1.G9, DRIVER1:STHV_0.IN2_0
unnamed: CONN_FPGA1:J1.H8, DRIVER1:IN0_1.1, DRIVER1:STHV_0.IN1_1
unnamed: CONN_FPGA1:J1.H7, DRIVER1:IN0_0.1, DRIVER1:STHV_0.IN1_0
unnamed: CONN_RESONATORS1:C30.2, DRIVER1:D0_0.A, DRIVER1:D0_1.C, DRIVER1:STHV_0.XDCR_1, DRIVER1:T_OUT_0.1
unnamed: CONN_RESONATORS1:C30.3, DRIVER1:D1_0.A, DRIVER1:D1_1.C, DRIVER1:STHV_0.XDCR_2, DRIVER1:T_OUT_1.1
unnamed: CONN_RESONATORS1:C30.4, DRIVER1:D2_0.A, DRIVER1:D2_1.C, DRIVER1:STHV_0.XDCR_3, DRIVER1:T_OUT_2.1
unnamed: CONN_RESONATORS1:C30.5, DRIVER1:D3_0.A, DRIVER1:D3_1.C, DRIVER1:STHV_0.XDCR_4, DRIVER1:T_OUT_3.1
unnamed: CONN_RESONATORS1:C30.6, DRIVER1:D4_0.A, DRIVER1:D4_1.C, DRIVER1:STHV_0.XDCR_5, DRIVER1:T_OUT_4.1
unnamed: CONN_RESONATORS1:C30.7, DRIVER1:D5_0.A, DRIVER1:D5_1.C, DRIVER1:STHV_0.XDCR_6, DRIVER1:T_OUT_5.1
unnamed: CONN_RESONATORS1:C30.8, DRIVER1:D6_0.A, DRIVER1:D6_1.C, DRIVER1:STHV_0.XDCR_7, DRIVER1:T_OUT_6.1
unnamed: CONN_RESONATORS1:C30.9, DRIVER1:D7_0.A, DRIVER1:D7_1.C, DRIVER1:STHV_0.XDCR_8, DRIVER1:T_OUT_7.1
unnamed: CONN_RESONATORS1:C30.10, DRIVER2:D0_0.A, DRIVER2:D0_1.C, DRIVER2:STHV_0.XDCR_1, DRIVER2:T_OUT_0.1
unnamed: CONN_RESONATORS1:C30.11, DRIVER2:D1_0.A, DRIVER2:D1_1.C, DRIVER2:STHV_0.XDCR_2, DRIVER2:T_OUT_1.1
unnamed: CONN_RESONATORS1:C30.12, DRIVER2:D2_0.A, DRIVER2:D2_1.C, DRIVER2:STHV_0.XDCR_3, DRIVER2:T_OUT_2.1
unnamed: CONN_RESONATORS1:C30.13, DRIVER2:D3_0.A, DRIVER2:D3_1.C, DRIVER2:STHV_0.XDCR_4, DRIVER2:T_OUT_3.1
unnamed: CONN_RESONATORS1:C30.14, DRIVER2:D4_0.A, DRIVER2:D4_1.C, DRIVER2:STHV_0.XDCR_5, DRIVER2:T_OUT_4.1
unnamed: CONN_RESONATORS1:C30.15, DRIVER2:D5_0.A, DRIVER2:D5_1.C, DRIVER2:STHV_0.XDCR_6, DRIVER2:T_OUT_5.1
unnamed: CONN_RESONATORS1:C30.16, DRIVER2:D6_0.A, DRIVER2:D6_1.C, DRIVER2:STHV_0.XDCR_7, DRIVER2:T_OUT_6.1
unnamed: CONN_RESONATORS1:C30.17, DRIVER2:D7_0.A, DRIVER2:D7_1.C, DRIVER2:STHV_0.XDCR_8, DRIVER2:T_OUT_7.1
POWER1:C3: POWER1:IC3.13, POWER1:L2.1
POWER1:E1: POWER1:D26.1, POWER1:IC3.2, POWER1:L7.1
POWER1:E2: POWER1:D25.1, POWER1:IC3.19, POWER1:L8.2
POWER1:FB1: POWER1:IC3.5, POWER1:R19.1, POWER1:R20.2
POWER1:FB2: POWER1:IC3.16, POWER1:R21.1, POWER1:R22.2
POWER1:GND: POWER1:C39.2, POWER1:C40.1, POWER1:C41.1, POWER1:C42.2, POWER1:C43.1, POWER1:C44.1, POWER1:C45.2, POWER1:C46.1, POWER1:C47.2, POWER1:D26.2, POWER1:IC3.9, POWER1:IC3.10, POWER1:IC3.11, POWER1:IC3.12, POWER1:IC3.21, POWER1:L8.1, POWER1:R18.1, POWER1:R20.1, POWER1:R22.1, POWER1:R25.2
POWER1:HVP_CW: POWER1:C40.2, POWER1:C45.1, POWER1:C46.2, POWER1:IC3.1, POWER1:IC3.20, POWER1:L2.2, POWER1:R17.1, POWER1:R18.2, POWER1:R23.1, POWER1:R24.2
POWER1:N5V: POWER1:C44.2, POWER1:D25.2, POWER1:R21.2
POWER1:OV/UV: POWER1:IC3.6, POWER1:R17.2
POWER1:P5V: POWER1:C43.2, POWER1:L7.2, POWER1:R19.2
POWER1:PG1: POWER1:IC3.4, POWER1:R24.1
POWER1:PG2: POWER1:IC3.17, POWER1:R23.2
POWER1:RT: POWER1:IC3.7, POWER1:R25.1
POWER1:SS1: POWER1:C41.2, POWER1:IC3.8
POWER1:SS2: POWER1:C42.1, POWER1:IC3.15
POWER1:VINT: POWER1:C39.1, POWER1:C47.1, POWER1:IC3.3, POWER1:IC3.14, POWER1:IC3.18
RECEIVER1:ADC2:+5V: RECEIVER1:ADC2:ADC1.30, RECEIVER1:ADC2:C142.1
RECEIVER1:ADC2:GND: RECEIVER1:ADC2:ADC1.9, RECEIVER1:ADC2:ADC1.11, RECEIVER1:ADC2:ADC1.13, RECEIVER1:ADC2:ADC1.14, RECEIVER1:ADC2:ADC1.20, RECEIVER1:ADC2:ADC1.29, RECEIVER1:ADC2:ADC1.31, RECEIVER1:ADC2:ADC1.32, RECEIVER1:ADC2:ADC1.EXP, RECEIVER1:ADC2:C139.2, RECEIVER1:ADC2:C140.2, RECEIVER1:ADC2:C141.2, RECEIVER1:ADC2:C142.2, RECEIVER1:ADC2:C143.2
RECEIVER1:ADC2:N1: RECEIVER1:ADC2:ADC1.26, RECEIVER1:ADC2:R2.1
RECEIVER1:ADC2:N2: RECEIVER1:ADC2:ADC1.25, RECEIVER1:ADC2:R1.1
RECEIVER1:ADC2:N$1: RECEIVER1:ADC2:ADC1.24, RECEIVER1:ADC2:R3.2
RECEIVER1:ADC2:N$2: RECEIVER1:ADC2:ADC1.23, RECEIVER1:ADC2:R4.2
RECEIVER1:ADC2:N$3: RECEIVER1:ADC2:ADC1.19, RECEIVER1:ADC2:R5.2
RECEIVER1:ADC2:N$4: RECEIVER1:ADC2:ADC1.18, RECEIVER1:ADC2:R6.2
RECEIVER1:ADC2:N$5: RECEIVER1:ADC2:ADC1.17, RECEIVER1:ADC2:R7.2
RECEIVER1:ADC2:N$81: RECEIVER1:ADC2:ADC1.10, RECEIVER1:ADC2:C139.1
RECEIVER1:ADC2:N$82: RECEIVER1:ADC2:ADC1.12, RECEIVER1:ADC2:C140.1
RECEIVER1:ADC2:N$83: RECEIVER1:ADC2:ADC1.28, RECEIVER1:ADC2:C141.1
RECEIVER1:ADC2:OVDD: RECEIVER1:ADC2:ADC1.21, RECEIVER1:ADC2:C143.1
RECEIVER1:N$1: RECEIVER1:S1:C14.2, RECEIVER1:S12:IC1.5
RECEIVER1:N$2: RECEIVER1:S1:C13.2, RECEIVER1:S12:IC1.3
RECEIVER1:N$3: RECEIVER1:S1:IC1.50, RECEIVER1:S12:C1.2, RECEIVER1:S12:C2.2, RECEIVER1:S12:C3.2, RECEIVER1:S12:C4.2, RECEIVER1:S12:R1.2, RECEIVER1:S12:R2.1
RECEIVER1:N$4: RECEIVER1:S1:C7.2, RECEIVER1:S6:C1.2, RECEIVER1:S6:C2.2, RECEIVER1:S6:C3.2, RECEIVER1:S6:C4.2, RECEIVER1:S6:R1.2, RECEIVER1:S6:R2.1
RECEIVER1:N$5: RECEIVER1:S1:C6.2, RECEIVER1:S6:IC1.3
RECEIVER1:N$6: RECEIVER1:S1:IC1.30, RECEIVER1:S6:IC1.5
RECEIVER1:N$7: RECEIVER1:S2:IC1.50, RECEIVER1:S5:C1.2, RECEIVER1:S5:C2.2, RECEIVER1:S5:C3.2, RECEIVER1:S5:C4.2, RECEIVER1:S5:R1.2, RECEIVER1:S5:R2.1
RECEIVER1:N$8: RECEIVER1:S2:C13.2, RECEIVER1:S5:IC1.3
RECEIVER1:N$9: RECEIVER1:S2:C14.2, RECEIVER1:S5:IC1.5
RECEIVER1:N$10: RECEIVER1:S2:C7.2, RECEIVER1:S7:C1.2, RECEIVER1:S7:C2.2, RECEIVER1:S7:C3.2, RECEIVER1:S7:C4.2, RECEIVER1:S7:R1.2, RECEIVER1:S7:R2.1
RECEIVER1:N$11: RECEIVER1:S2:C6.2, RECEIVER1:S7:IC1.3
RECEIVER1:N$12: RECEIVER1:S2:IC1.30, RECEIVER1:S7:IC1.5
RECEIVER1:N$13: RECEIVER1:ADC2:ADC1.8, RECEIVER1:S12:C4.1, RECEIVER1:S12:R4.1
RECEIVER1:N$14: RECEIVER1:ADC2:ADC1.5, RECEIVER1:S12:C3.1, RECEIVER1:S12:R3.1
RECEIVER1:N$15: RECEIVER1:ADC2:ADC1.4, RECEIVER1:S6:C4.1, RECEIVER1:S6:R4.1
RECEIVER1:N$16: RECEIVER1:ADC2:ADC1.3, RECEIVER1:S6:C3.1, RECEIVER1:S6:R3.1
RECEIVER1:N$17: RECEIVER1:ADC2:ADC1.2, RECEIVER1:S5:C4.1, RECEIVER1:S5:R4.1
RECEIVER1:N$18: RECEIVER1:ADC2:ADC1.1, RECEIVER1:S5:C3.1, RECEIVER1:S5:R3.1
RECEIVER1:N$19: RECEIVER1:S7:C4.1, RECEIVER1:S7:R4.1
RECEIVER1:N$20: RECEIVER1:S7:C3.1, RECEIVER1:S7:R3.1
RECEIVER1:S1:+5V: RECEIVER1:S1:L27.1, RECEIVER1:S1:L28.1, RECEIVER1:S1:L29.1, RECEIVER1:S1:L30.1, RECEIVER1:S1:L31.1, RECEIVER1:S1:L32.1, RECEIVER1:S1:R1.2, RECEIVER1:S1:R2.2, RECEIVER1:S1:R3.2, RECEIVER1:S1:R9.2, RECEIVER1:S1:R11.2, RECEIVER1:S1:R13.2
RECEIVER1:S1:CLAMP12_1: RECEIVER1:S1:C22.1, RECEIVER1:S1:IC1.53, RECEIVER1:S1:R4.2
RECEIVER1:S1:CLAMP12_2: RECEIVER1:S1:C21.1, RECEIVER1:S1:IC1.28, RECEIVER1:S1:R5.2
RECEIVER1:S1:EN12: RECEIVER1:S1:IC1.52, RECEIVER1:S1:R9.1
RECEIVER1:S1:EN34: RECEIVER1:S1:IC1.51, RECEIVER1:S1:R13.1
RECEIVER1:S1:GAIN12_1: RECEIVER1:S1:C20.1, RECEIVER1:S1:IC1.54, RECEIVER1:S1:R3.1, RECEIVER1:S1:VR1.3
RECEIVER1:S1:GAIN12_2: RECEIVER1:S1:C19.1, RECEIVER1:S1:IC1.27, RECEIVER1:S1:R1.1, RECEIVER1:S1:VR2.3
RECEIVER1:S1:GND: RECEIVER1:S1:C5.2, RECEIVER1:S1:C8.1, RECEIVER1:S1:C9.1, RECEIVER1:S1:C10.1, RECEIVER1:S1:C19.2, RECEIVER1:S1:C20.2, RECEIVER1:S1:C21.2, RECEIVER1:S1:C22.2, RECEIVER1:S1:C24.1, RECEIVER1:S1:C27.1, RECEIVER1:S1:C51.1, RECEIVER1:S1:C52.1, RECEIVER1:S1:C53.1, RECEIVER1:S1:C54.1, RECEIVER1:S1:C55.1, RECEIVER1:S1:C56.1, RECEIVER1:S1:D1.1, RECEIVER1:S1:D1.2, RECEIVER1:S1:D2.1, RECEIVER1:S1:D2.2, RECEIVER1:S1:IC1.3, RECEIVER1:S1:IC1.14, RECEIVER1:S1:IC1.17, RECEIVER1:S1:IC1.18, RECEIVER1:S1:IC1.21, RECEIVER1:S1:IC1.32, RECEIVER1:S1:IC1.60, RECEIVER1:S1:IC1.63, RECEIVER1:S1:IC1.64, RECEIVER1:S1:IC1.65, RECEIVER1:S1:R4.1, RECEIVER1:S1:R5.1, RECEIVER1:S1:R6.1, RECEIVER1:S1:R10.1, RECEIVER1:S1:TP2_GND1.1, RECEIVER1:S1:VR1.1, RECEIVER1:S1:VR1.2, RECEIVER1:S1:VR2.1, RECEIVER1:S1:VR2.2
RECEIVER1:S1:HILO_12: RECEIVER1:S1:IC1.29, RECEIVER1:S1:R6.2, RECEIVER1:S1:R11.1
RECEIVER1:S1:INH2: RECEIVER1:S1:C11.2, RECEIVER1:S1:C23.1, RECEIVER1:S1:C24.2, RECEIVER1:S1:IC1.1
RECEIVER1:S1:INH4: RECEIVER1:S1:C12.1, RECEIVER1:S1:C26.1, RECEIVER1:S1:C27.2, RECEIVER1:S1:IC1.16
RECEIVER1:S1:MODE_12: RECEIVER1:S1:IC1.41, RECEIVER1:S1:R2.1, RECEIVER1:S1:R10.2
RECEIVER1:S1:N$1: RECEIVER1:S1:C5.1, RECEIVER1:S1:IC1.61, RECEIVER1:S1:R7.2
RECEIVER1:S1:N$2: RECEIVER1:S1:C8.2, RECEIVER1:S1:IC1.20, RECEIVER1:S1:R8.1
RECEIVER1:S1:N$4: RECEIVER1:S1:IC1.33, RECEIVER1:S1:IC1.39, RECEIVER1:S1:IC1.42, RECEIVER1:S1:IC1.48
RECEIVER1:S1:N$5: RECEIVER1:S1:C10.2, RECEIVER1:S1:IC1.2
RECEIVER1:S1:N$6: RECEIVER1:S1:C9.2, RECEIVER1:S1:IC1.15
RECEIVER1:S1:N$11: RECEIVER1:S1:C23.2, RECEIVER1:S1:L1.2
RECEIVER1:S1:N$12: RECEIVER1:S1:C11.1, RECEIVER1:S1:R15.2
RECEIVER1:S1:N$13: RECEIVER1:S1:C26.2, RECEIVER1:S1:L6.2
RECEIVER1:S1:N$14: RECEIVER1:S1:C12.2, RECEIVER1:S1:R12.1
RECEIVER1:S1:N$15: RECEIVER1:S1:IC1.19, RECEIVER1:S1:R8.2
RECEIVER1:S1:R1_I: RECEIVER1:S1:IC1.62, RECEIVER1:S1:R7.1
RECEIVER1:S1:R1_LO_N: RECEIVER1:S1:C1.1, RECEIVER1:S1:IC1.13, RECEIVER1:S1:R12.2
RECEIVER1:S1:R1_LO_P: RECEIVER1:S1:C2.1, RECEIVER1:S1:IC1.12
RECEIVER1:S1:R1_V1I_N: RECEIVER1:S1:C1.2, RECEIVER1:S1:IC1.10
RECEIVER1:S1:R1_V1I_P: RECEIVER1:S1:C2.2, RECEIVER1:S1:IC1.11
RECEIVER1:S1:R1_V1O_N: RECEIVER1:S1:C4.1, RECEIVER1:S1:IC1.37, RECEIVER1:S1:TP2_6.1
RECEIVER1:S1:R1_V1O_P: RECEIVER1:S1:C3.1, RECEIVER1:S1:IC1.38, RECEIVER1:S1:TP2_5.1
RECEIVER1:S1:R1_V2I_N: RECEIVER1:S1:C3.2, RECEIVER1:S1:IC1.25
RECEIVER1:S1:R1_V2I_P: RECEIVER1:S1:C4.2, RECEIVER1:S1:IC1.24
RECEIVER1:S1:R1_V2O_N: RECEIVER1:S1:C6.1, RECEIVER1:S1:IC1.35, RECEIVER1:S1:TP2_7.1
RECEIVER1:S1:R1_V2O_P: RECEIVER1:S1:C7.1, RECEIVER1:S1:IC1.34, RECEIVER1:S1:TP2_8.1
RECEIVER1:S1:R2_LO_N: RECEIVER1:S1:C15.2, RECEIVER1:S1:IC1.4, RECEIVER1:S1:R15.1
RECEIVER1:S1:R2_LO_P: RECEIVER1:S1:C16.2, RECEIVER1:S1:IC1.5
RECEIVER1:S1:R2_V1I_N: RECEIVER1:S1:C15.1, RECEIVER1:S1:IC1.7
RECEIVER1:S1:R2_V1I_P: RECEIVER1:S1:C16.1, RECEIVER1:S1:IC1.6
RECEIVER1:S1:R2_V1O_N: RECEIVER1:S1:C17.1, RECEIVER1:S1:IC1.44, RECEIVER1:S1:TP2_9.1
RECEIVER1:S1:R2_V1O_P: RECEIVER1:S1:C18.1, RECEIVER1:S1:IC1.43, RECEIVER1:S1:TP2_10.1
RECEIVER1:S1:R2_V2I_N: RECEIVER1:S1:C17.2, RECEIVER1:S1:IC1.56
RECEIVER1:S1:R2_V2I_P: RECEIVER1:S1:C18.2, RECEIVER1:S1:IC1.57
RECEIVER1:S1:R2_V2O_N: RECEIVER1:S1:C14.1, RECEIVER1:S1:IC1.46, RECEIVER1:S1:TP2_11.1
RECEIVER1:S1:R2_V2O_P: RECEIVER1:S1:C13.1, RECEIVER1:S1:IC1.47, RECEIVER1:S1:TP2_12.1
RECEIVER1:S1:VPS1_1: RECEIVER1:S1:C55.2, RECEIVER1:S1:IC1.55, RECEIVER1:S1:L31.2
RECEIVER1:S1:VPS2_1: RECEIVER1:S1:C51.2, RECEIVER1:S1:IC1.8, RECEIVER1:S1:L27.2
RECEIVER1:S1:VPS3_1: RECEIVER1:S1:C52.2, RECEIVER1:S1:IC1.9, RECEIVER1:S1:L28.2
RECEIVER1:S1:VPS4_1: RECEIVER1:S1:C53.2, RECEIVER1:S1:IC1.26, RECEIVER1:S1:L29.2
RECEIVER1:S1:VPS12_1: RECEIVER1:S1:C56.2, RECEIVER1:S1:IC1.45, RECEIVER1:S1:L32.2
RECEIVER1:S1:VPS34_1: RECEIVER1:S1:C54.2, RECEIVER1:S1:IC1.36, RECEIVER1:S1:L30.2
RECEIVER1:S2:+5V: RECEIVER1:S2:L27.1, RECEIVER1:S2:L28.1, RECEIVER1:S2:L29.1, RECEIVER1:S2:L30.1, RECEIVER1:S2:L31.1, RECEIVER1:S2:L32.1, RECEIVER1:S2:R1.2, RECEIVER1:S2:R2.2, RECEIVER1:S2:R3.2, RECEIVER1:S2:R9.2, RECEIVER1:S2:R11.2, RECEIVER1:S2:R13.2
RECEIVER1:S2:CLAMP12_1: RECEIVER1:S2:C22.1, RECEIVER1:S2:IC1.53, RECEIVER1:S2:R4.2
RECEIVER1:S2:CLAMP12_2: RECEIVER1:S2:C21.1, RECEIVER1:S2:IC1.28, RECEIVER1:S2:R5.2
RECEIVER1:S2:EN12: RECEIVER1:S2:IC1.52, RECEIVER1:S2:R9.1
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

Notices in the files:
parts and their libraries:
Wurth_Elektronik_Passive_Capacitors_rev1: Copyright: Würth Elektronik
SparkFun-Resistors: Licensing: Creative Commons ShareAlike 4.0 International - https://creativecommons.org/licenses/by-sa/4.0
